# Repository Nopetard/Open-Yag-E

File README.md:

# Open-Yag-E
Open source laser led cutter engraver project

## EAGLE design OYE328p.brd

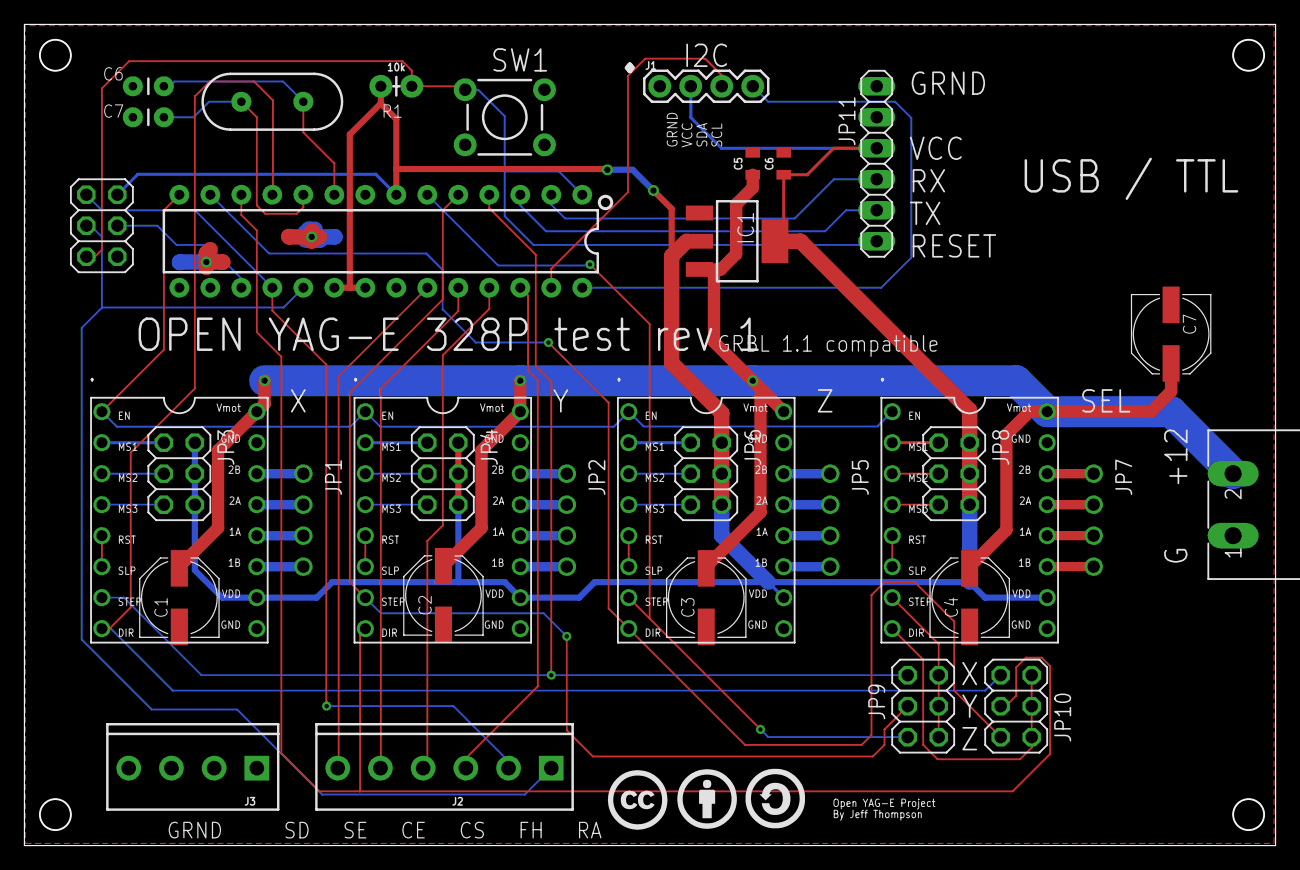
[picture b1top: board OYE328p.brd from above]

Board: 2 copper layers, 102.4 x 67.1 mm, 34 parts (0 on the bottom side), 58 nets.

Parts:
ATMEGA328-1:C1, ATMEGA328-1:C2: 22pF; CAP-PTH-2.54
ATMEGA328-1:JP1: 2X03
ATMEGA328-1:R1: 10k; AXIAL-0.1
ATMEGA328-1:S1: MOMENTARY-SWITCH-SPST-PTH-6.0MM; TACTILE_SWITCH_PTH_6.0MM
ATMEGA328-1:U1: 328P; DIP28
ATMEGA328-1:Y1: 16MHz; HC49US
C1, C2, C3, C4, C7: PANASONIC_D
C5, C6: 10uF; 0805
IC1: SOT223
J1: 1X04
J2: SCREWTERMINAL-3.5MM-6
J3: SCREWTERMINAL-3.5MM-4
JP1, JP2, JP5, JP7: 1X04
JP3, JP4, JP6, JP8, JP9, JP10: 2X03
JP11: 1X06
U$1, U$2, U$3, U$4: A4988BREAKOUT
X1: MSTBA2

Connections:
+12V: C1.+, C2.+, C3.+, C4.+, C5.1, C7.+, IC1.3, U$1.VMOT, U$2.VMOT, U$3.VMOT, U$4.VMOT, X1.2
ATMEGA328-1:N$1: ATMEGA328-1:C1.2, ATMEGA328-1:U1.9, ATMEGA328-1:Y1.2
ATMEGA328-1:N$2: ATMEGA328-1:C2.2, ATMEGA328-1:U1.10, ATMEGA328-1:Y1.1
ATMEGA328-1:N$6: ATMEGA328-1:JP1.4, ATMEGA328-1:U1.17
GND: ATMEGA328-1:C1.1, ATMEGA328-1:C2.1, ATMEGA328-1:JP1.6, ATMEGA328-1:S1.3, ATMEGA328-1:U1.8, ATMEGA328-1:U1.22, C1.-, C2.-, C3.-, C4.-, C5.2, C6.2, C7.-, IC1.1, J1.1, J3.1, J3.2, J3.3, J3.4, JP11.1, U$1.GND, U$1.GND@0, U$2.GND, U$2.GND@0, U$3.GND, U$3.GND@0, U$4.GND, U$4.GND@0, X1.1
unnamed: JP4.1, U$2.MS1
unnamed: JP4.3, U$2.MS2
unnamed: JP4.5, U$2.MS3
unnamed: JP2.1, U$2.2B
unnamed: JP2.2, U$2.2A
unnamed: JP2.3, U$2.1A
unnamed: JP2.4, U$2.1B
unnamed: JP3.1, U$1.MS1
unnamed: JP3.3, U$1.MS2
unnamed: JP3.5, U$1.MS3
unnamed: U$2.RST, U$2.SLP
unnamed: JP6.1, U$3.MS1
unnamed: JP1.1, U$1.2B
unnamed: JP1.2, U$1.2A
unnamed: JP1.3, U$1.1A
unnamed: JP1.4, U$1.1B
unnamed: JP6.3, U$3.MS2
unnamed: JP6.5, U$3.MS3
unnamed: JP5.1, U$3.2B
unnamed: JP5.2, U$3.2A
unnamed: JP5.3, U$3.1A
unnamed: JP5.4, U$3.1B
unnamed: U$3.RST, U$3.SLP
unnamed: JP8.1, U$4.MS1
unnamed: JP8.3, U$4.MS2
unnamed: JP8.5, U$4.MS3
unnamed: JP7.1, U$4.2B
unnamed: JP7.2, U$4.2A
unnamed: JP7.3, U$4.1A
unnamed: JP7.4, U$4.1B
unnamed: U$4.RST, U$4.SLP
unnamed: ATMEGA328-1:U1.14, U$1.EN, U$2.EN, U$3.EN, U$4.EN
unnamed: ATMEGA328-1:U1.4, JP9.6, U$1.STEP
unnamed: ATMEGA328-1:U1.11, JP10.6, U$1.DIR
unnamed: ATMEGA328-1:U1.5, JP9.4, U$2.STEP
unnamed: ATMEGA328-1:U1.12, JP10.4, U$2.DIR
unnamed: ATMEGA328-1:U1.6, JP9.2, U$3.STEP
unnamed: ATMEGA328-1:U1.13, JP10.2, U$3.DIR
unnamed: JP9.1, JP9.3, JP9.5, U$4.STEP
unnamed: JP10.1, JP10.3, JP10.5, U$4.DIR
unnamed: ATMEGA328-1:JP1.3, ATMEGA328-1:U1.19, J2.1
unnamed: ATMEGA328-1:JP1.1, ATMEGA328-1:U1.18, J2.2
unnamed: ATMEGA328-1:U1.26, J2.3
unnamed: ATMEGA328-1:U1.25, J2.4
unnamed: ATMEGA328-1:U1.24, J2.5
unnamed: ATMEGA328-1:U1.23, J2.6
unnamed: ATMEGA328-1:U1.2, JP11.4
unnamed: ATMEGA328-1:U1.3, JP11.5
unnamed: ATMEGA328-1:JP1.5, ATMEGA328-1:R1.P$1, ATMEGA328-1:S1.1, ATMEGA328-1:U1.1, JP11.6
unnamed: ATMEGA328-1:U1.28, J1.4
unnamed: ATMEGA328-1:U1.27, J1.3
unnamed: U$1.RST, U$1.SLP
VCC: ATMEGA328-1:JP1.2, ATMEGA328-1:R1.P$2, ATMEGA328-1:U1.7, ATMEGA328-1:U1.20, ATMEGA328-1:U1.21, C6.1, IC1.2, IC1.4, J1.2, JP3.2, JP3.4, JP3.6, JP4.2, JP4.4, JP4.6, JP6.2, JP6.4, JP6.6, JP8.2, JP8.4, JP8.6, JP11.3, U$1.VDD, U$2.VDD, U$3.VDD, U$4.VDD

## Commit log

2018-11-25 Initial upload
    This is the early eagle files for the Yag-E board plus the gerber files. This is untested board at this point. only tested on a breadboard.

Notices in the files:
parts and their libraries:
SparkFun-Capacitors: Licensing: Creative Commons ShareAlike 4.0 International - https://creativecommons.org/licenses/by-sa/4.0
